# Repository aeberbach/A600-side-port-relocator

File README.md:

# A600 right side port relocator

(what do you even name this thing?)

It's just a trio of connectors with a PCB between. The A600 has its ports for mouse and game controllers on the right. The joystick port is right up against a pice of plastic molding so you can't get anything but a slim plug in there. Wires connected to either port will tend to stick out to the right and get in the way of the mouse. It was a pretty horrible place to put these ports but maybe it was the cheapest.

The idea is that this device plugs into the side of the Amiga 600 and the two ports are relocated using a single stacked connector at the back of the machine. The mouse port is on the bottom and hopefully the mouse cord gets in the way less there. The joystick port is on top and is probably easier to reach, also joysticks with large plugs can be used. Either port can have wide (i.e. DIY) connectors plugged in.

A single-sided PCB is used to keep cost as low as possible and because it costs no extra to use thick fibreglass, it is thick to make it sturdy. The 3D printed cover is optional but recommended, it covers the electrical connections of the ports underneath the PCB just in case you decide to put your Amiga on a conductive surface. It looks nicer too.

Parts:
Stacked DE-9 male pair: https://www.digikey.com.au/product-detail/en/L17H2110130/L17H2110130-ND/
Single DE-9 female: https://www.digikey.com.au/product-detail/en/ID09S33E4GX00LF/609-5771-ND

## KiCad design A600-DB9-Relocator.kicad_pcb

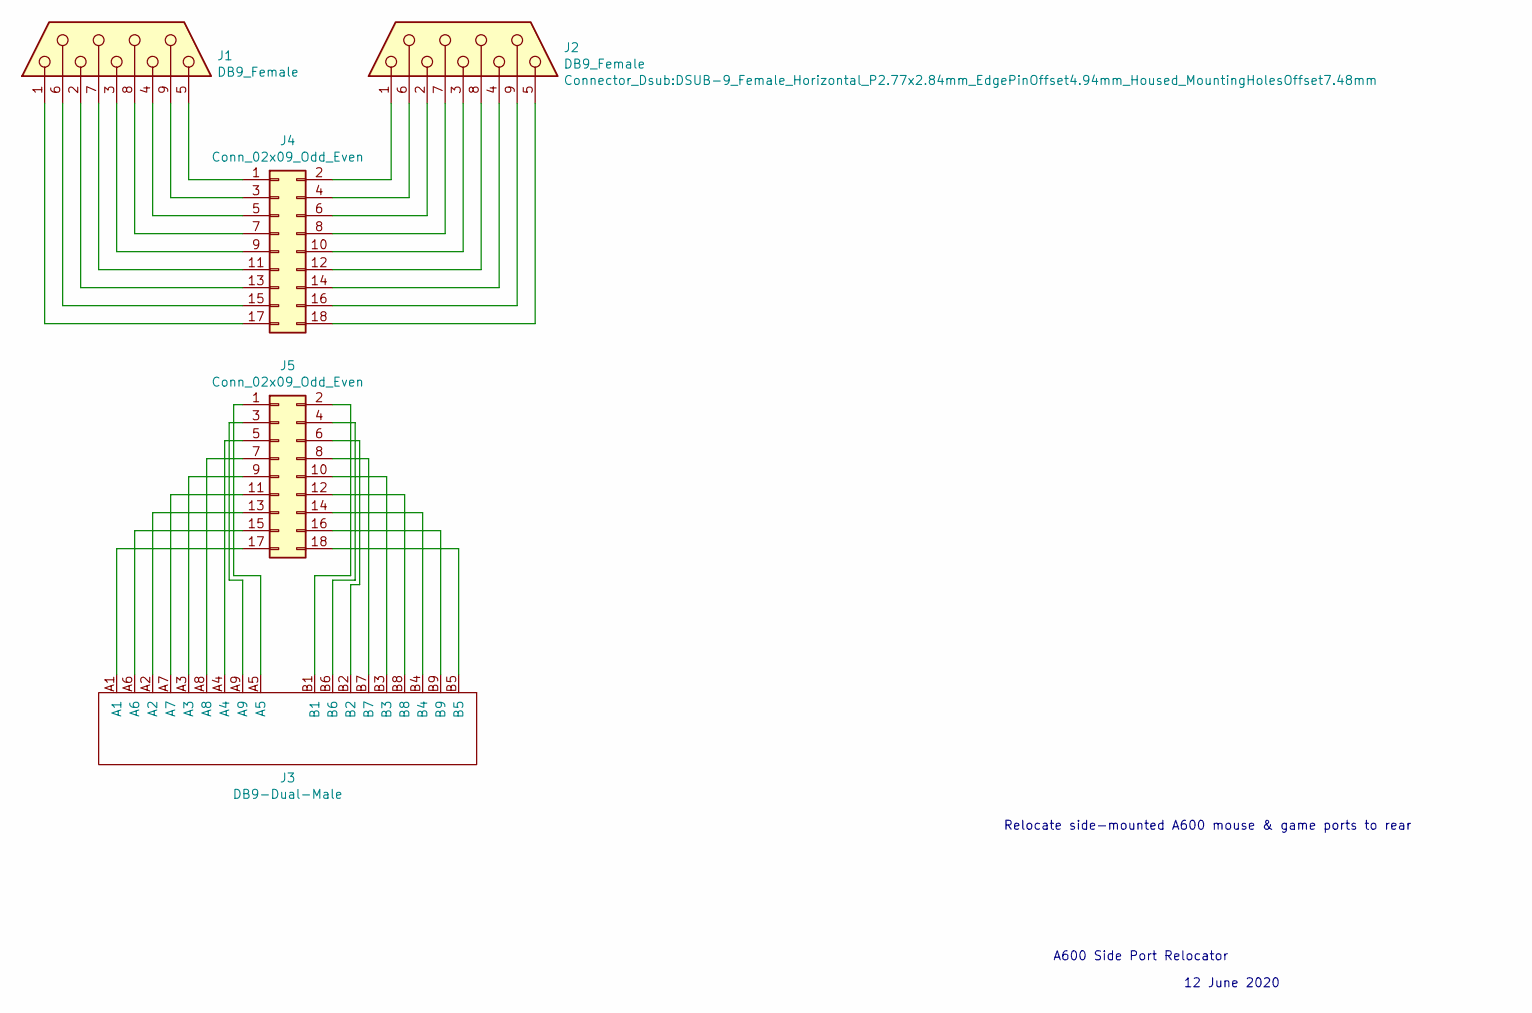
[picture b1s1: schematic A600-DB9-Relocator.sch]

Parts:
J1, J2: DB9_Female; DSUB-9_Female_Horizontal_P2.77x2.84mm_EdgePinOffset4.94mm_H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
J3: DB9-Dual-Male; CONN-DUAL-D-SUB-9POS-RA-SLDR
J4, J5: Conn_02x09_Odd_Even; PinHeader_2x09_P2.54mm_Vertical

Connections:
unnamed: J1.1, J4.17
unnamed: J1.2, J4.13
unnamed: J1.3, J4.9
unnamed: J1.4, J4.5
unnamed: J1.5, J4.1
unnamed: J1.6, J4.15
unnamed: J1.7, J4.11
unnamed: J1.8, J4.7
unnamed: J1.9, J4.3
unnamed: J2.1, J4.2
unnamed: J2.2, J4.6
unnamed: J2.3, J4.10
unnamed: J2.4, J4.14
unnamed: J2.5, J4.18
unnamed: J2.6, J4.4
unnamed: J2.7, J4.8
unnamed: J2.8, J4.12
unnamed: J2.9, J4.16
unnamed: J3.A1, J5.17
unnamed: J3.A2, J5.13
unnamed: J3.A3, J5.9
unnamed: J3.A4, J5.5
unnamed: J3.A5, J5.1
unnamed: J3.A6, J5.15
unnamed: J3.A7, J5.11
unnamed: J3.A8, J5.7
unnamed: J3.A9, J5.3
unnamed: J3.B1, J5.2
unnamed: J3.B2, J5.6
unnamed: J3.B3, J5.10
unnamed: J3.B4, J5.14
unnamed: J3.B5, J5.18
unnamed: J3.B6, J5.4
unnamed: J3.B7, J5.8
unnamed: J3.B8, J5.12
unnamed: J3.B9, J5.16

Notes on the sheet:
Relocate side-mounted A600 mouse & game ports to rear
A600 Side Port Relocator
12 June 2020

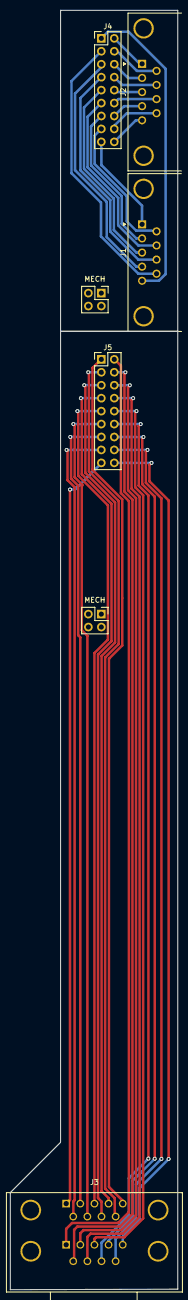
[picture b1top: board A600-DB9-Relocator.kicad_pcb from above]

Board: 2 copper layers, 32.9 x 251.1 mm, 7 parts (0 on the bottom side), 36 nets.

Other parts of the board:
MECH: PinSocket_2x02_P2.54mm_Vertical
MECH#2: PinSocket_2x02_P2.54mm_Vertical

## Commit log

2020-06-12 Initial commit of project files
2020-06-12 gitignore
2020-06-12 add readme
2020-09-30 PCB complete
2020-10-01 Corrected routing; title block
2020-10-01 Add digikey part numbers for the connectors

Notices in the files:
A600-DB9-Relocator.kicad_pcb:
MIT License
